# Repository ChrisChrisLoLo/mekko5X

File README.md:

# mekko5X

Part cyberdeck, part ortholinear. With 2 knobs and 2 large OLED displays, this keyboard can be used for animations, displaying information, or for controlling a GUI. The small form factor makes the board a unique ortholinear keyboard, or a powerful macropad. It could also double as a MIDI controller!

Powered by a Raspberry Pi Pico, this keyboard should have more than enough space and power for any kind of firmware you have in mind!

## Status
Pre-prototyping phase. Playing around with setting up the OLED drivers, and will look into how to get it working with QMK. Testing pending. Copy and build if you're sure you know what you're doing. BYO firmware.

## Features
- 2 Rotary encoders
- 2 Oled displays on a SPI bus
- 4x10 matrix
- Powered by an RP2040

## Acknowledgements
Big thank you to [PCBWay](https://www.pcbway.com/) for greenlighting and sponsoring a project such as this! Overtime, I've come to appretiate the quality of the silkscreen and soldermask boards I get from PCBWay, and would strongly consider them if I had to sell or give a quality PCB to a friend or and customer. PCBWay has also given back to the community by supporting projects like these, so I strongly recommend them if you're looking to make a board for yourself!

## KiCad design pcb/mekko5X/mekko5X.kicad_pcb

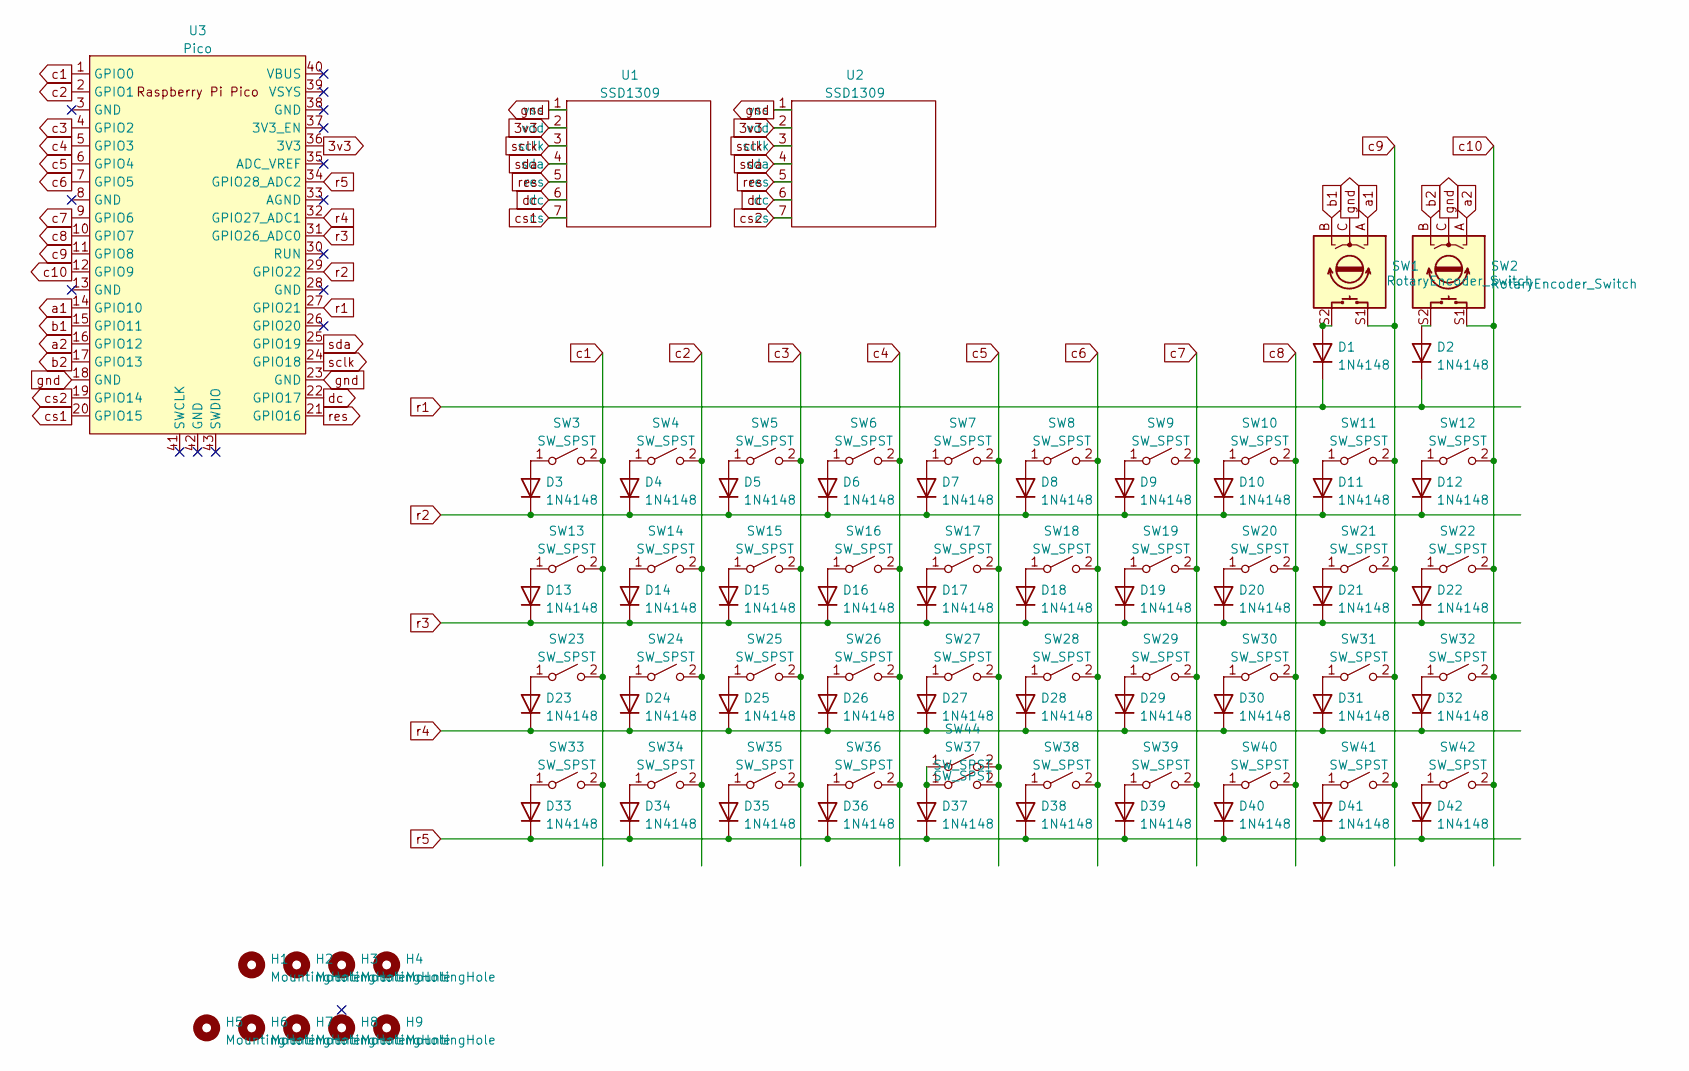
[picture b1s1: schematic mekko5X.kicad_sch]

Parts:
D1, D2, D3, D4, D5, D6, D7, D8, D9, D10, D11, D12, D13, D14, D15, D16, D17, D18, D19, D20, D21, D22, D23, D24, D25, D26, D27, D28, D29, D30, D31, D32, D33, D34, D35, D36, D37, D38, D39, D40, D41, D42: 1N4148
H1, H2, H3, H4, H5, H6, H7, H8, H9: MountingHole; MountingHole_2.2mm_M2_DIN965
SW1, SW2: RotaryEncoder_Switch; RotaryEncoder_Alps_EC11E-Switch_Vertical_H20mm
SW3, SW4, SW5, SW6, SW7, SW8, SW9, SW10, SW11, SW12, SW13, SW14, SW15, SW16, SW17, SW18, SW19, SW20, SW21, SW22, SW23, SW24, SW25, SW26, SW27, SW28, SW29, SW30, SW31, SW32, SW33, SW34, SW35, SW36, SW37, SW38, SW39, SW40, SW41, SW42, SW44: SW_SPST; Kailh_socket_MX
U1, U2: SSD1309; 2.4_inch_OLED
U3: Pico; RPi_Pico_SMD_TH

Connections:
3v3: U1.2 (vdd), U2.2 (vdd), U3.36 (3V3)
unnamed: D1.2 (A), SW1.S2
unnamed: D2.2 (A), SW2.S2
unnamed: D3.2 (A), SW3.1 (A)
unnamed: D4.2 (A), SW4.1 (A)
unnamed: D5.2 (A), SW5.1 (A)
unnamed: D6.2 (A), SW6.1 (A)
unnamed: D7.2 (A), SW7.1 (A)
unnamed: D8.2 (A), SW8.1 (A)
unnamed: D9.2 (A), SW9.1 (A)
unnamed: D10.2 (A), SW10.1 (A)
unnamed: D11.2 (A), SW11.1 (A)
unnamed: D12.2 (A), SW12.1 (A)
unnamed: D13.2 (A), SW13.1 (A)
unnamed: D14.2 (A), SW14.1 (A)
unnamed: D15.2 (A), SW15.1 (A)
unnamed: D16.2 (A), SW16.1 (A)
unnamed: D17.2 (A), SW17.1 (A)
unnamed: D18.2 (A), SW18.1 (A)
unnamed: D19.2 (A), SW19.1 (A)
unnamed: D20.2 (A), SW20.1 (A)
unnamed: D21.2 (A), SW21.1 (A)
unnamed: D22.2 (A), SW22.1 (A)
unnamed: D23.2 (A), SW23.1 (A)
unnamed: D24.2 (A), SW24.1 (A)
unnamed: D25.2 (A), SW25.1 (A)
unnamed: D26.2 (A), SW26.1 (A)
unnamed: D27.2 (A), SW27.1 (A)
unnamed: D28.2 (A), SW28.1 (A)
unnamed: D29.2 (A), SW29.1 (A)
unnamed: D30.2 (A), SW30.1 (A)
unnamed: D31.2 (A), SW31.1 (A)
unnamed: D32.2 (A), SW32.1 (A)
unnamed: D33.2 (A), SW33.1 (A)
unnamed: D34.2 (A), SW34.1 (A)
unnamed: D35.2 (A), SW35.1 (A)
unnamed: D36.2 (A), SW36.1 (A)
unnamed: D37.2 (A), SW37.1 (A), SW44.1 (A)
unnamed: D38.2 (A), SW38.1 (A)
unnamed: D39.2 (A), SW39.1 (A)
unnamed: D40.2 (A), SW40.1 (A)
unnamed: D41.2 (A), SW41.1 (A)
unnamed: D42.2 (A), SW42.1 (A)
a1: SW1.A, U3.14 (GPIO10)
a2: SW2.A, U3.16 (GPIO12)
b1: SW1.B, U3.15 (GPIO11)
b2: SW2.B, U3.17 (GPIO13)
c1: SW3.2 (B), SW13.2 (B), SW23.2 (B), SW33.2 (B), U3.1 (GPIO0)
c2: SW4.2 (B), SW14.2 (B), SW24.2 (B), SW34.2 (B), U3.2 (GPIO1)
c3: SW5.2 (B), SW15.2 (B), SW25.2 (B), SW35.2 (B), U3.4 (GPIO2)
c4: SW6.2 (B), SW16.2 (B), SW26.2 (B), SW36.2 (B), U3.5 (GPIO3)
c5: SW7.2 (B), SW17.2 (B), SW27.2 (B), SW37.2 (B), SW44.2 (B), U3.6 (GPIO4)
c6: SW8.2 (B), SW18.2 (B), SW28.2 (B), SW38.2 (B), U3.7 (GPIO5)
c7: SW9.2 (B), SW19.2 (B), SW29.2 (B), SW39.2 (B), U3.9 (GPIO6)
c8: SW10.2 (B), SW20.2 (B), SW30.2 (B), SW40.2 (B), U3.10 (GPIO7)
c9: SW1.S1, SW11.2 (B), SW21.2 (B), SW31.2 (B), SW41.2 (B), U3.11 (GPIO8)
c10: SW2.S1, SW12.2 (B), SW22.2 (B), SW32.2 (B), SW42.2 (B), U3.12 (GPIO9)
cs1: U1.7 (cs), U3.20 (GPIO15)
cs2: U2.7 (cs), U3.19 (GPIO14)
dc: U1.6 (dc), U2.6 (dc), U3.22 (GPIO17)
gnd: SW1.C, SW2.C, U1.1 (vss), U2.1 (vss), U3.18 (GND), U3.23 (GND)
r1: D1.1 (K), D2.1 (K), U3.27 (GPIO21)
r2: D3.1 (K), D4.1 (K), D5.1 (K), D6.1 (K), D7.1 (K), D8.1 (K), D9.1 (K), D10.1 (K), D11.1 (K), D12.1 (K), U3.29 (GPIO22)
r3: D13.1 (K), D14.1 (K), D15.1 (K), D16.1 (K), D17.1 (K), D18.1 (K), D19.1 (K), D20.1 (K), D21.1 (K), D22.1 (K), U3.31 (GPIO26_ADC0)
r4: D23.1 (K), D24.1 (K), D25.1 (K), D26.1 (K), D27.1 (K), D28.1 (K), D29.1 (K), D30.1 (K), D31.1 (K), D32.1 (K), U3.32 (GPIO27_ADC1)
r5: D33.1 (K), D34.1 (K), D35.1 (K), D36.1 (K), D37.1 (K), D38.1 (K), D39.1 (K), D40.1 (K), D41.1 (K), D42.1 (K), U3.34 (GPIO28_ADC2)
res: U1.5 (res), U2.5 (res), U3.21 (GPIO16)
sclk: U1.3 (sclk), U2.3 (sclk), U3.24 (GPIO18)
sda: U1.4 (sda), U2.4 (sda), U3.25 (GPIO19)

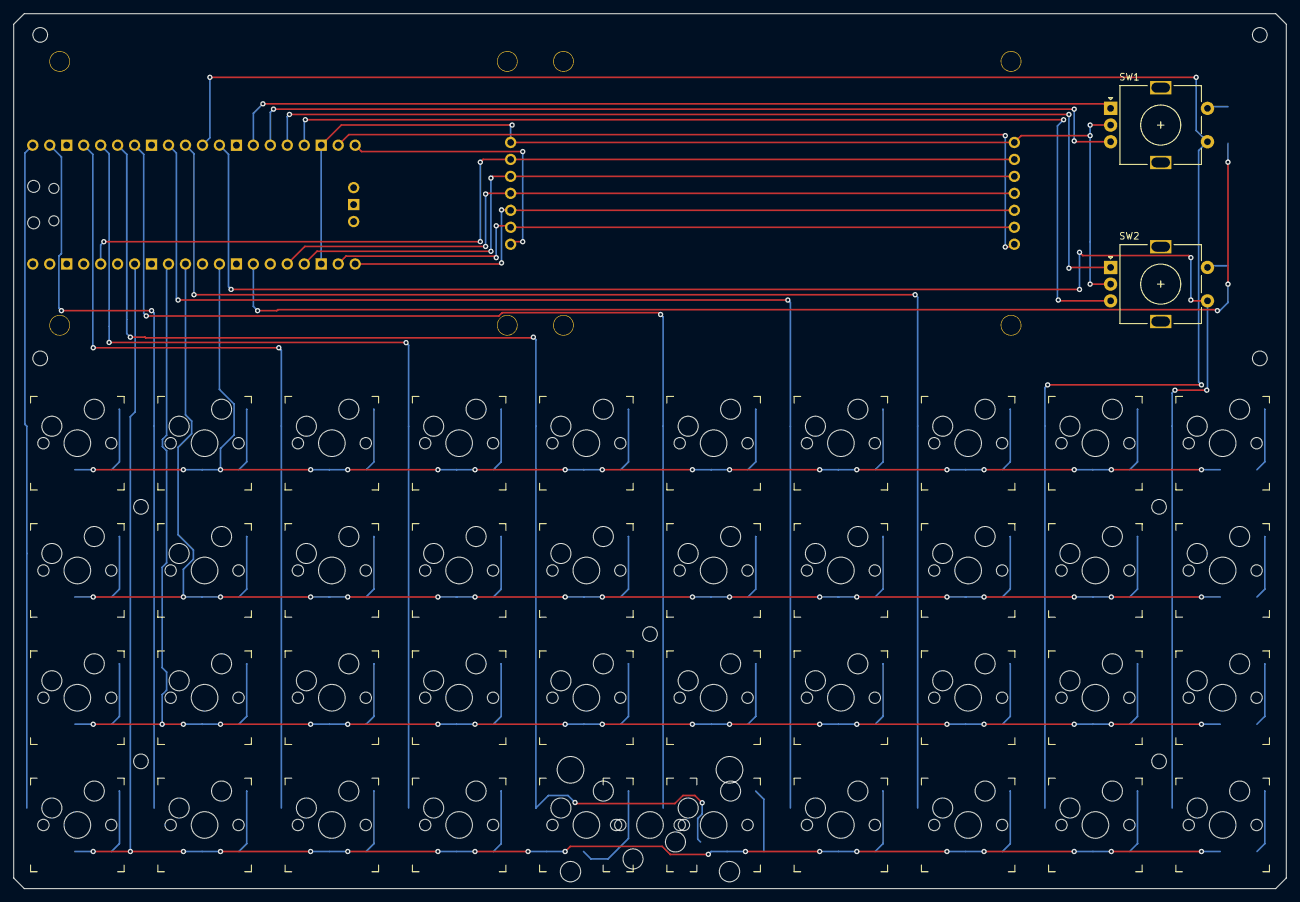
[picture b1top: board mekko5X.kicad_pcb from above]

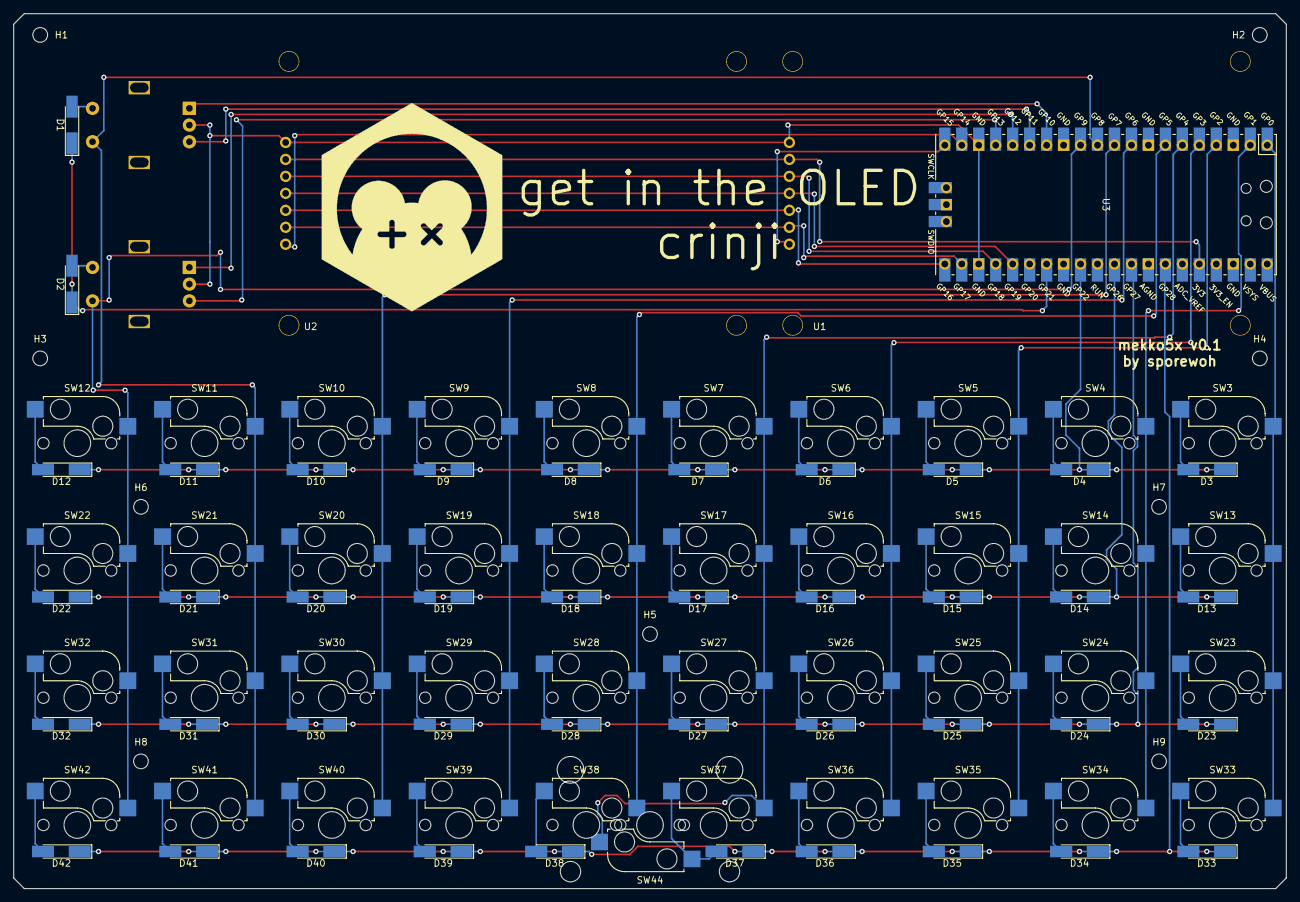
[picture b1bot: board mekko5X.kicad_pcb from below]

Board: 2 copper layers, 190.5 x 131.0 mm, 97 parts (52 on the bottom side), 69 nets.

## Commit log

2022-08-30 kicad init
2022-09-02 add v0 pcb
2022-10-10 add files
